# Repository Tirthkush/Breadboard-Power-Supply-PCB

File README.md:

# Breadboard Power Supply PCB

A compact Breadboard Power Supply PCB designed in **KiCad** to provide regulated **5V and 3.3V outputs** from a **12V DC input**.

This is my **second PCB design project**, following my first simple pocket torch PCB. The goal of this project was to design a practical power supply that can later be used for breadboard-based electronics and embedded systems projects.

## Features

- 12V DC barrel jack input
- Regulated 5V output using LM7805
- Regulated 3.3V output using LM317
- Power ON/OFF switch
- LED power indicator
- Filtering capacitors
- Multiple output connectors
- Designed using KiCad

## Circuit Overview

The PCB accepts a 12V DC input through a barrel jack. The input is then distributed to two regulation stages:

- **LM7805** provides the regulated 5V output.
- **LM317** is configured to provide approximately 3.3V output.

Filtering capacitors are included around the power stages to help provide stable supply rails.

## Design Process

The PCB was developed completely in KiCad through the following workflow:

    Circuit Planning
          ↓
    Schematic Design
          ↓
    Component Selection
          ↓
    Footprint Assignment
          ↓
    PCB Layout
          ↓
    Component Placement
          ↓
    Routing
          ↓
    Design Rule Check
          ↓
    3D PCB Visualization

## KiCad Design

The project includes the KiCad design files:

- Schematic
- PCB layout
- Component footprints
- 3D PCB view
- Bill of Materials (BOM)
- Gerber files for future fabrication

## Applications

The intended use of this PCB is to provide convenient power rails for:

- Breadboard prototypes
- Microcontroller projects
- Sensor modules
- Embedded systems experiments
- General electronics projects

## What I Learned

Through this project, I gained practical experience with:

- Schematic capture in KiCad
- Component selection
- Footprint assignment
- PCB component placement
- PCB routing
- Voltage regulation circuits
- Design Rule Checking (DRC)
- PCB 3D visualization
- Preparing a PCB design for future fabrication

This project helped me understand the transition from a circuit idea to a complete PCB design ready for manufacturing.

## Future Plans

The next step is to get the PCB fabricated, assemble the components, and test the actual 5V and 3.3V output rails.

Future revisions could also include:

- Reverse-polarity protection
- Input fuse/protection
- USB power outputs
- More efficient switching regulators
- Improved thermal management

## Project Status

**Schematic Design ✅**  
**PCB Layout ✅**  
**3D Design ✅**  
**Fabrication ⏳**  
**Assembly ⏳**  
**Testing ⏳**

## Author

**Tirth Kushwaha**

Electronics & Telecommunication Engineering Student

Interested in **Embedded Systems, IoT, Embedded Hardware, Robotics, and Automotive Electronics**.

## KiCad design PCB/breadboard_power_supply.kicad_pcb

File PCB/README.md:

# PCB Layout

This folder contains the **KiCad PCB layout** for the Breadboard Power Supply PCB.

The PCB layout was developed from the schematic and includes the **component placement, footprints, copper tracks, power connections, and board layout** for the 12V input, 5V regulation, and 3.3V regulation sections.

The PCB layout was designed with consideration for **component placement, routing, connectivity, and ease of assembly**.

**Software:** KiCad

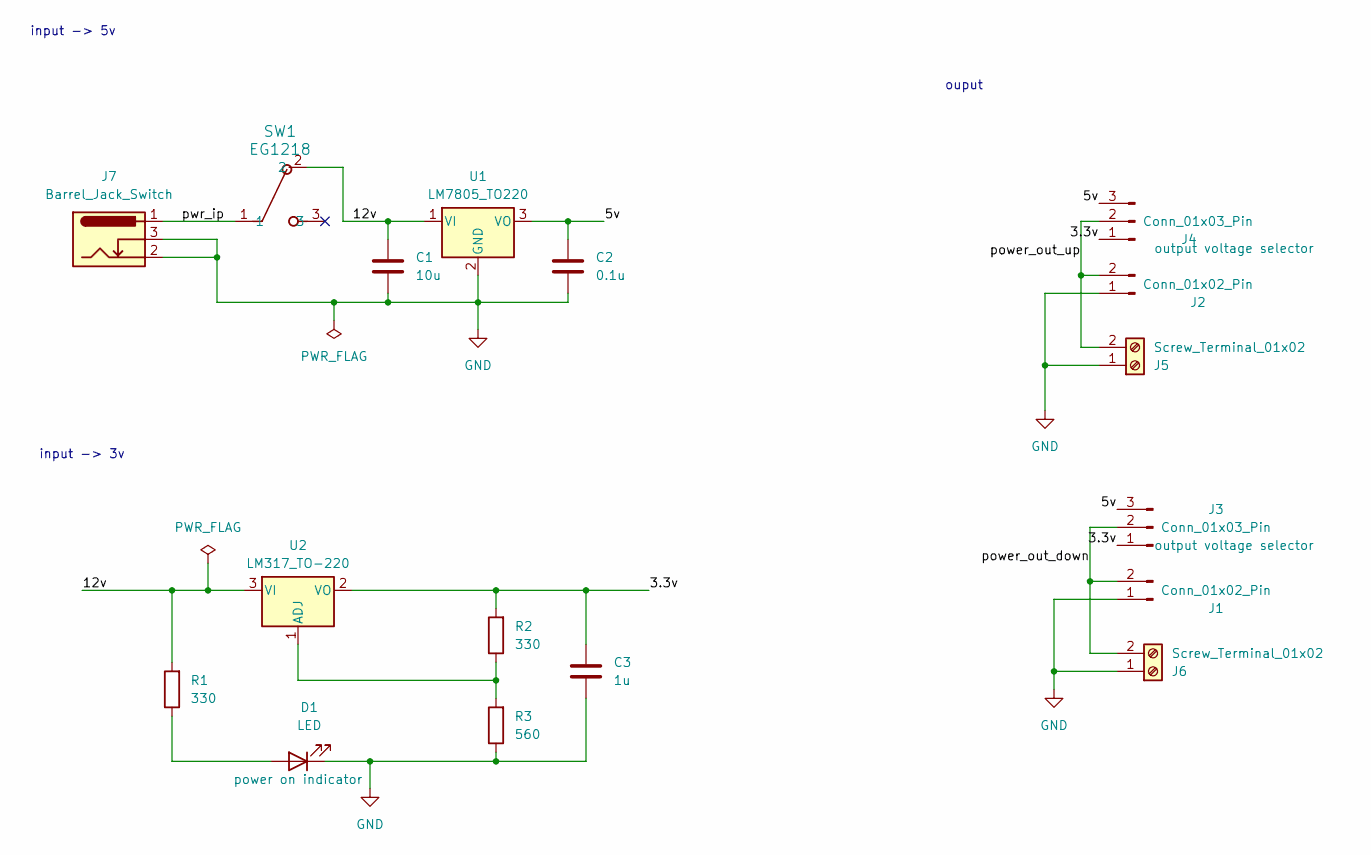
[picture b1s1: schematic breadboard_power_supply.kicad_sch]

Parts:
C1: 10u; C_Disc_D3.0mm_W1.6mm_P2.50mm
C2: 0.1u; C_Disc_D3.0mm_W1.6mm_P2.50mm
C3: 1u; C_Disc_D3.0mm_W1.6mm_P2.50mm
D1: LED; LED_D5.0mm
J1, J2: Conn_01x02_Pin; PinHeader_1x02_P2.54mm_Vertical
J3, J4: Conn_01x03_Pin; PinHeader_1x03_P2.54mm_Vertical
J5, J6: Screw_Terminal_01x02; TerminalBlock_bornier-2_P5.08mm
J7: Barrel_Jack_Switch; BarrelJack_Kycon_KLDX-0202-xC_Horizontal
R1, R2: 330; R_Axial_DIN0204_L3.6mm_D1.6mm_P1.90mm_Vertical
R3: 560; R_Axial_DIN0204_L3.6mm_D1.6mm_P1.90mm_Vertical
SW1: EG1218; SW_Slide_SPDT_Straight_CK_OS102011MS2Q
U1: LM7805_TO220; TO-220-3_Vertical
U2: LM317_TO-220; TO-220-3_Vertical

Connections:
/3.3v: C3.1, J3.1, J4.1, R2.2, U2.2 (VO)
/5v: C2.1, J3.3, J4.3, U1.3 (VO)
/12v: C1.1, R1.2, SW1.2, U1.1 (VI), U2.3 (VI)
/power_out_down: J1.2, J3.2, J6.2
/power_out_up: J2.2, J4.2, J5.2
/pwr_ip: J7.1, SW1.1
GND: C1.2, C2.2, C3.2, D1.1 (K), J1.1, J2.1, J5.1, J6.1, J7.2, J7.3, R3.1, U1.2 (GND)
unnamed: D1.2 (A), R1.1
unnamed: R2.1, R3.2, U2.1 (ADJ)

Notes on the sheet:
ouput
input -> 5v
input -> 3v

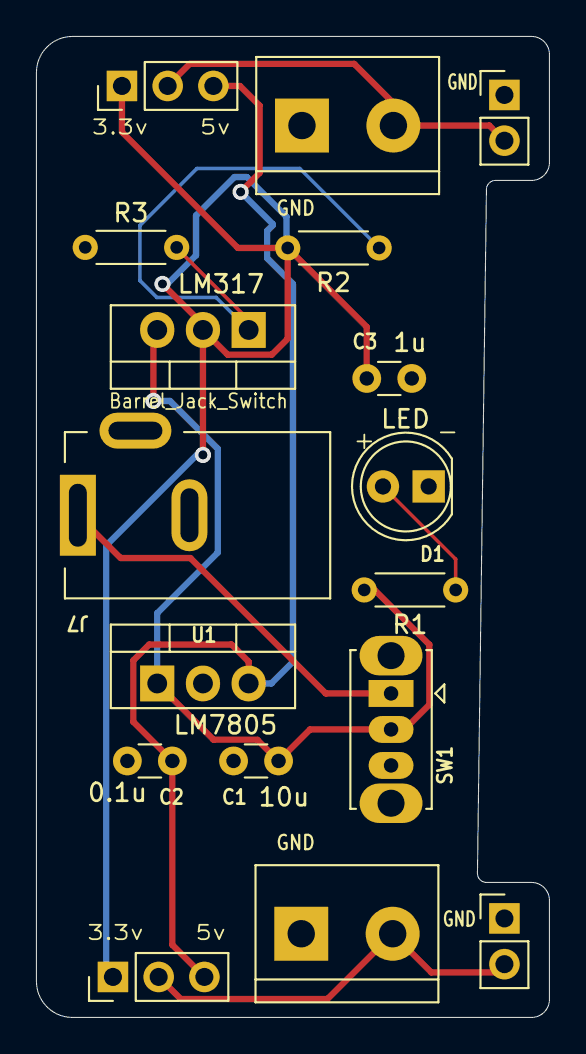
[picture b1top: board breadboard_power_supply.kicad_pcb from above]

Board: 2 copper layers, 28.5 x 54.5 mm, 17 parts (0 on the bottom side), 9 nets.
